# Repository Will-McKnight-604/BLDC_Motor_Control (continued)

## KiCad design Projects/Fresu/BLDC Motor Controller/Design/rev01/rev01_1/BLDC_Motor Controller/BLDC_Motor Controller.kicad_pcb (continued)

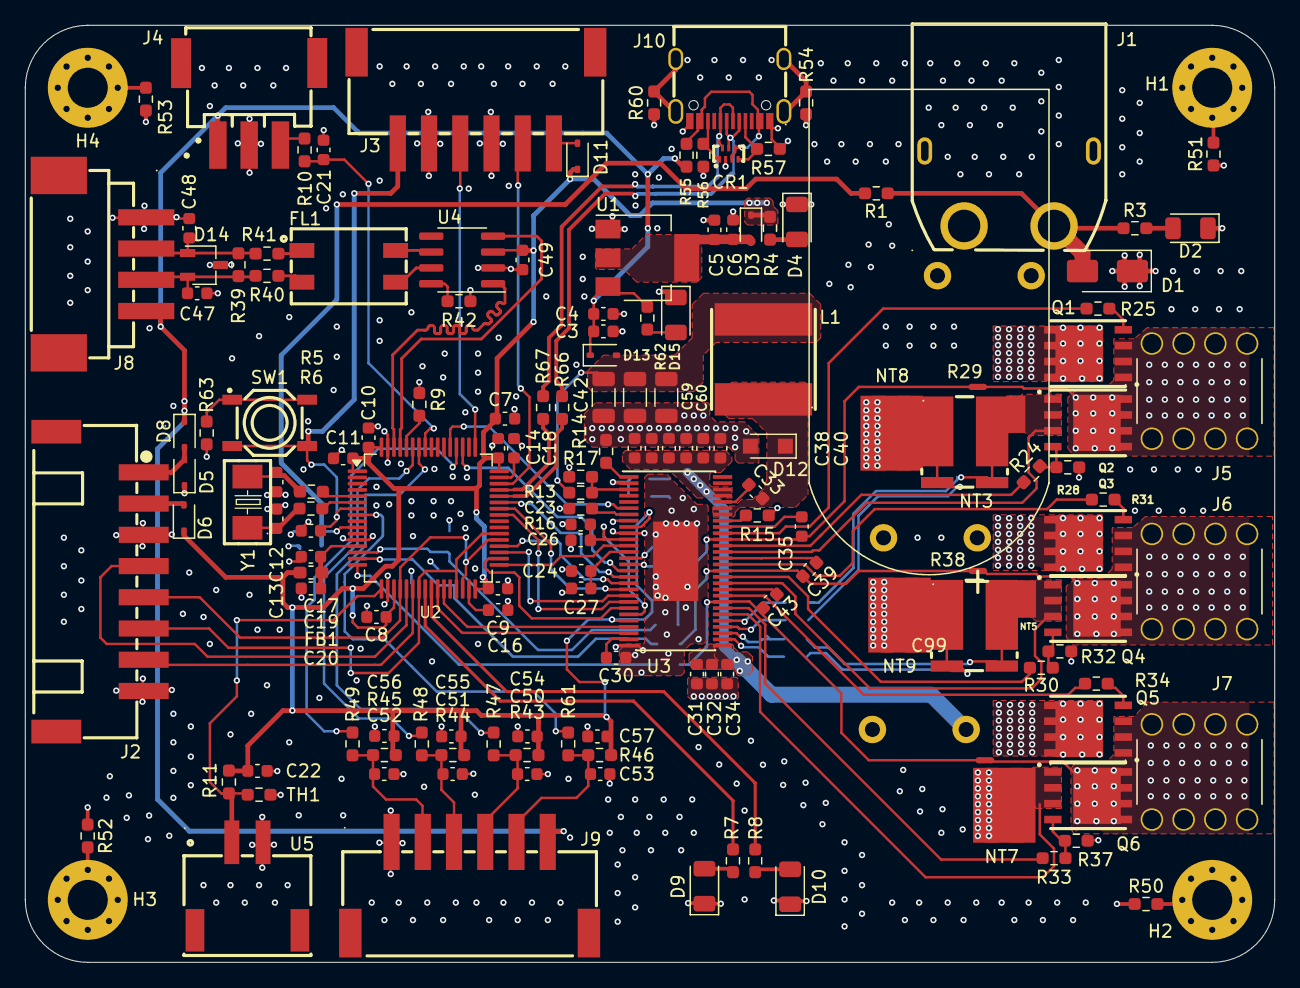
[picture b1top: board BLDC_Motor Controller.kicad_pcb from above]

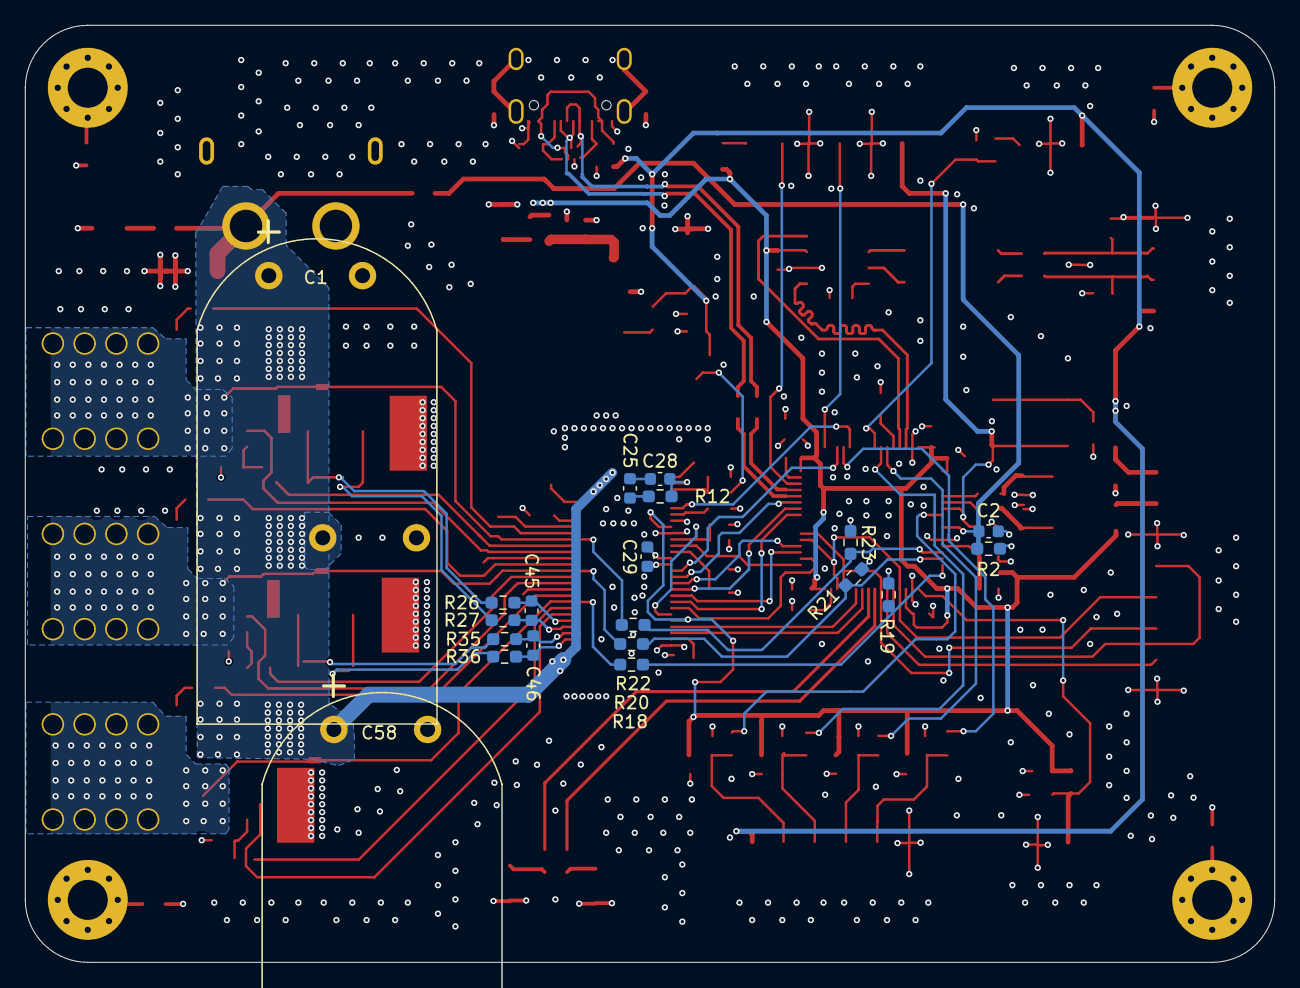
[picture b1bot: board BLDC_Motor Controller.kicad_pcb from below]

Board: 4 copper layers, 100.0 x 75.0 mm, 178 parts (20 on the bottom side), 126 nets.

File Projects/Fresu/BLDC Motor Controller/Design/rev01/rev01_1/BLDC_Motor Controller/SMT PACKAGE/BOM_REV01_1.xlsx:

Designator | Footprint | Quantity | Manufacturer Part Number | JLCPCB Part Number | Comment | Supplier 1 | Supplier 2 | Supplier 3 | Price Total | Substitute 1 | Substitute 2
C10, C11, C14, C17, C19, C21, C22, C54, C55, C56, C57, C8, C9 | 0603 (Imperial) | 16 | CC0603KRX7R6BB104 | C519438 | 100nF 0603 10V ±10% | LCSC
C12, C13 | 0603 (Imperial) | 2 | 06035A100KAT2A | C597129 | 10pF 0603 50V ±10% | LCSC
C16, C18, C23, C24, C26, C27, C30, C49 | 0603 (Imperial) | 8 | CL10A225KQ8NNNC | C71000 | 2.2uF 0603 6.3V ±10% | LCSC
C20, C3, C4, C5, C6 | 0603 (Imperial) | 5 | CL10A105KP8NNNC | C26413 | 1uF 0603 10V ±10% | LCSC
C25 | 0603 (Imperial) | 1 | CC0603KRX7R9BB103 | C100042 | 10nF 0603 50V ±10% | LCSC
C28 | 0603 (Imperial) | 1 | CC0603KRX7R9BB121 | C107072 | 120pF 0603 50V ±10% | LCSC
C29 | 0603 (Imperial) | 1 | CC0603KRX7R0BB223 | C313105 | 22nF 0603 100V ±10% | LCSC
C31, C32, C34, C36, C37, C38, C40, C41, C44,C35, C39, C43, C2,C33 | 0603 (Imperial) | 10 | CL10B104KC8NNNC | C15725 | 100nF 0603 100V ±10% | LCSC
C45, C46 | 0603 (Imperial) | 2 | CC0603KRX7R9BB222 | C107082 | 2.2nF 50V ±10% 0603 | LCSC
C47, C48 | 0603 (Imperial) | 2 | CC0603JRNPO9BN510 | C107051 | 51pF 50V ±5% 0603 | LCSC
C50, C51, C52, C53 | 0603 (Imperial) | 4 | 0603B472K500NT | C53987 | 4.7nF 50V ±10% 0603 | LCSC
C7 | 0603 (Imperial) | 1 | CL10A106MP8NNNC | C85713 | 10uF 0603 10V ±10% | LCSC
FB1 | 0603 (Imperial) | 1 | BLM18PG121SN1D | C14709 | 120 OHM @100MHz 0603 Ferrite Beads | LCSC
R1, R18, R20, R22, R28, R3, R32, R37 | 0603 (Imperial) | 8 | 0603WAF3902T5E | C23153 | 39k OHM 0603 RES ±1% | LCSC
R10, R11, R19, R2, R21, R23, R43, R44, R45 | 0603 (Imperial) | 9 | 0603WAF2201T5E | C4190 | 2.2k OHM 0603 RES ±1% | LCSC
R12 | 0603 (Imperial) | 1 | 0603WAF1602T5E | C4210 | 16k OHM 0603 RES ±1% | LCSC
R13, R42, R46, R47, R48, R49 | 0603 (Imperial) | 7 | 0603WAF1002T5E | C25804 | 10k OHM 0603 RES ±1% | LCSC
R14 | 0603 (Imperial) | 1 | FRC0603F2053TS | C5126104 | 205k OHM 0603 RES ±1% | LCSC
R15 | 0603 (Imperial) | 1 | 0603WAF1004T5E | C22935 | 1M OHM 0603 RES ±1% | LCSC
R16 | 0603 (Imperial) | 1 | 0603WAF1802T5E | C25810 | 18k OHM 0603 RES ±1% | LCSC
R17 | 0603 (Imperial) | 1 | 0603WAF3301T5E | C22978 | 3.3k OHM 0603 RES ±1% | LCSC
R24, R25, R30, R31, R33, R34 | 0603 (Imperial) | 6 | 0603WAF470KT5E | C23164 | 4.7 OHM 0603 RES ±1% | LCSC
R26, R27, R35, R36, R9 | 0603 (Imperial) | 5 | 0603WAF1000T5E | C22775 | 100 OHM 0603 RES ±1% | LCSC
R39 | 0603 (Imperial) | 1 | 0603WAF1200T5E | C22787 | 120 OHM 0603 RES ±1% | LCSC
R4, R62, R7, R8 | 0603 (Imperial) | 4 | 0603WAF1001T5E | C21190 | 1k OHM 0603 RES ±1% | LCSC
R40, R41 | 0603 (Imperial) | 2 | 0603WAF100JT5E | C22859 | 10 OHM 0603 RES ±1% | LCSC
R5, R50, R51, R52, R53, R54, R55, R6, R60, R61 | 0603 (Imperial) | 10 | 0603WAF0000T5E | C21189 | 0 OHM 0603 RES ±1% | LCSC
R56, R57 | 0603 (Imperial) | 2 | 0603WAF5101T5E | C23186 | 5.1k OHM 0603 RES ±1% | LCSC
R58, R59 | 0603 (Imperial) | 2 | 0603WAF220JT5E | C23345 | 22 OHM 0603 RES ±1% | LCSC
TH1 | 0603 (Imperial) | 1 | NCP18XH103F03RB | C13564 | 10k OHM 0603 NTC Thermistors | LCSC
D10 | 1206 (Imperial) | 1 | 15-21/R6C-FQ1R1B/2T | C93133 | Red 1206 Light Emitting Diodes | LCSC
D15, D2, D4, D9 | 1206 (Imperial) | 4 | 15-21/GHC-XS1T1/2T | C131257 | Emerald 1206 Light Emitting Diodes | LCSC
C42, C59, C60 | 1210 (Imperial) | 3 | EMK325BJ106KN-T | C92769 | 10uF 1206 16V ±10% | LCSC
J2 | CONN-SMD_8P-P2.50_HX25003-8AWB | 1 | HX25003-8AWB | C442367 | Conn_01x08 | LCSC
J8 | CONN-SMD_S4B-XH-SM4-TB-LF-SN | 1 | S4B-XH-SM4-TB(LF)(SN) | C161861 | Conn_01x04 | LCSC
J3, J9 | CONN-SMD_S6B-XH-SM4-TB-LF-SN | 2 | C2905028 | C2905028 | 1x6P XH 1 2.5mm Male pin 6 | LCSC
U5 | CONN-SMD_XH-2PWBPZ | 1 | XH-2PWBPZ | C2687444 | XH-2PWBPZ | LCSC
J4 | CONN-SMD_XH-3AWB | 1 | C141812 | C141812 | Conn_01x03 | LCSC
J1 | CONN-TH_XT60PW-M | 1 | XT60PW-M | C98732 | XT60PW-M | TME
Y1 | CRYSTAL-SMD_L5.0-W3.2 | 1 | X50328MSB2GI | C115962 | 8MHz Crystal | LCSC
D11, D13, D3, D6, D8 | D_SOD-323 | 5 | LRB551V-30T1G | C62119 | BAT60A | LCSC
D5 | D_SOD-323 | 1 | PESD3V3U1UA,115 | C403915 | PESD3V3U1UA,115 | LCSC
D7 | D_SOD-323 | 1 | PTVSHC3D15VUH | C312234 | SD05-7 | LCSC
FL1 | FILTER-SMD_4P-L9.2-W6.0-P2.54-TL | 1 | 744227S | C2651119 | CMC 51UH 1A 2LN 5.5K OHM SMD | Digikey
U3 | HTSSOP-56-1EP_6.1x14mm_P0.5mm_EP3.61x6.35mm | 1 | DRV8302DCA | C84672 | DRV8302DCA | LCSC
L1 | IND-SMD_L7.8-W7.8_SDR0805 | 1 | SDR0805-220ML | C139488 | 22uH FIXED IND 1.5A 110 MOHM SMD | LCSC
U2 | LQFP-64_10x10mm_P0.5mm | 1 | STM32F405RGT6 | C15742 | STM32F405RGTx | LCSC
Printed Circuit Board | PCB | 1 | PCB_DF_ESC_rev01_1 |  | Bare Printed Circuit Board | JLCPC | PCBWAY |  | $1.48
C1, C58 | Plugin, Radial D16xL25mm | 2 | LKMI2501K821MF | C443097 | 820uF 80V 32m Ohm@100kHz ±20% | LCSC | Digikey -TBC |  |  | 80ZLH820MEFC18X25
Q1, Q2, Q3, Q4, Q5, Q6 | PQFN-8_L6.0-W5.0-P1.27-LS6.0-BL | 6 | HSBA15810C | C845605 | 100V 100A 4.5m?@10V,30A 208W 4V@250uA N Channel PQFN-8(5x6) MOSFETs | LCSC
R29, R38 | RES-SMD_L7.0-W6.7 | 2 | WSLP27261L000FEA | C500635 | RES 0.001 OHM 1% 7W 2726 | LCSC
D1 | SMA | 1 | SMAJ60A | C707480 | SMAJ60A | LCSC
D12 | SOD-123W_L2.9-W2.1-LS4.4-RD | 1 | PMEG6020ER,115 | C98663 | PMEG6020 | LCSC
U4 | SOIC-8_3.9x4.9mm_P1.27mm | 1 | SN65HVD230DR | C12084 | SN65HVD230 | LCSC
U1 | SOT-223 | 1 | AMS1117-3.3 | C347222 | AMS1117-3.3 | LCSC
SW1 | SW-SMD_4P-L5.2-W5.2-P3.70-LS6.4 | 1 | PTS526SK15SMTR2LFS | C2689521 | SW_DIP_x01 | LCSC
D14 | TSOT-23 | 1 | ESDCAN24-2BLY | C5158050 | ESDCAN24-2BLY | LCSC
J10 | USB-C_SMD-TYPE-C-31-M-12 | 1 | TYPE-C-31-M-12 | C165948 | TYPE-C-31-M-12 | LCSC
J5, J6, J7 | WE_7461084 | 3 | 7461084 | C6828431 | 160A TERM REDCUBE M6 8PIN PCB | Digikey
CR1 | XSON-7_L2.2-W1.2-P0.50-BL | 1 | PUSB3AB6Z | C553550 | PUSB3AB6Z | LCSC
 |  |  |  |  |  |  |  |  |  |  |  |  |  |  |  |  |  | S

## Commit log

2024-01-06 Repo Location Change
    Moved Project Files to better organized location
2024-01-07 Update 2
    Created Project, schematic and pcb templates
2024-01-07 Update 3
    Created flat hierarchy and pages, now just need to define them
2024-01-07 Update 4
    Started Block Diagram page
2024-01-09 Update 5
    nearly completed MCU schematic, PDF version is wrong so waiting for it to be fixed
2024-01-13 UPDATE 6
    Completed MCU schematic Page
2024-01-13 UPDATE 7
    COMPLETED MOSFET SCHEMATIC
2024-01-13 UPDATE 8
    COMPLETED CAN SCHEMATIC
2024-01-13 UPDATE 9
    COMPLETED FILTERS SCHEMATIC
2024-01-13 UPDATE 10
    COMPELTED STEP-DOWN SCHEMATAIC
2024-01-13 UPDATE 11
    INPUT PROTECTION SCHEMATIC COMPLETE
2024-02-04 Update 12
    added files, like BOM, 3D step files course uses
2024-02-11 Update 13
    Added:
    1) USB Schematic
    2) footprints to all parts
2024-02-11 Update 14
    Added 4 mounting holes, imported all components into PCB project, created board outline
2024-02-11 Update 15
    Fixing some schematic errors
    initial layout of larger component complete
2024-02-12 Update 16
    Almost finished placing all the components on the board as rough placement
2024-02-17 Update 17
    Started laying out the driver and the main FET power polygons
2024-02-19 Update 18
    almost done routing driver chip and MCU (first pass)
2024-02-19 Update 19
    further MCU layout
2024-02-19 Update 20
    First layout completed, all tracks laid
2024-02-19 Update 21
    Now all tracks are laid, working on DRC
2024-02-19 Update 22
    Continued DRC
2024-02-25 Update 23
    Converted to Kicad 8
    Working on DRC
2024-02-25 Update 24
    DRC Complete
    Generating MFR'ing files
2024-03-03 Update 25
    Capturing all updates
2024-03-03 Update 26
    Matched DF's Designators to mine so I can use BOM as is
    Updated MFR'ing files
    Rev1 Ready for release
